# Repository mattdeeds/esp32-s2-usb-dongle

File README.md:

# esp32-s2-usb-dongle
 Simple USB A dongle with ESP32-S2-WROVER module for usb peripheral emulation

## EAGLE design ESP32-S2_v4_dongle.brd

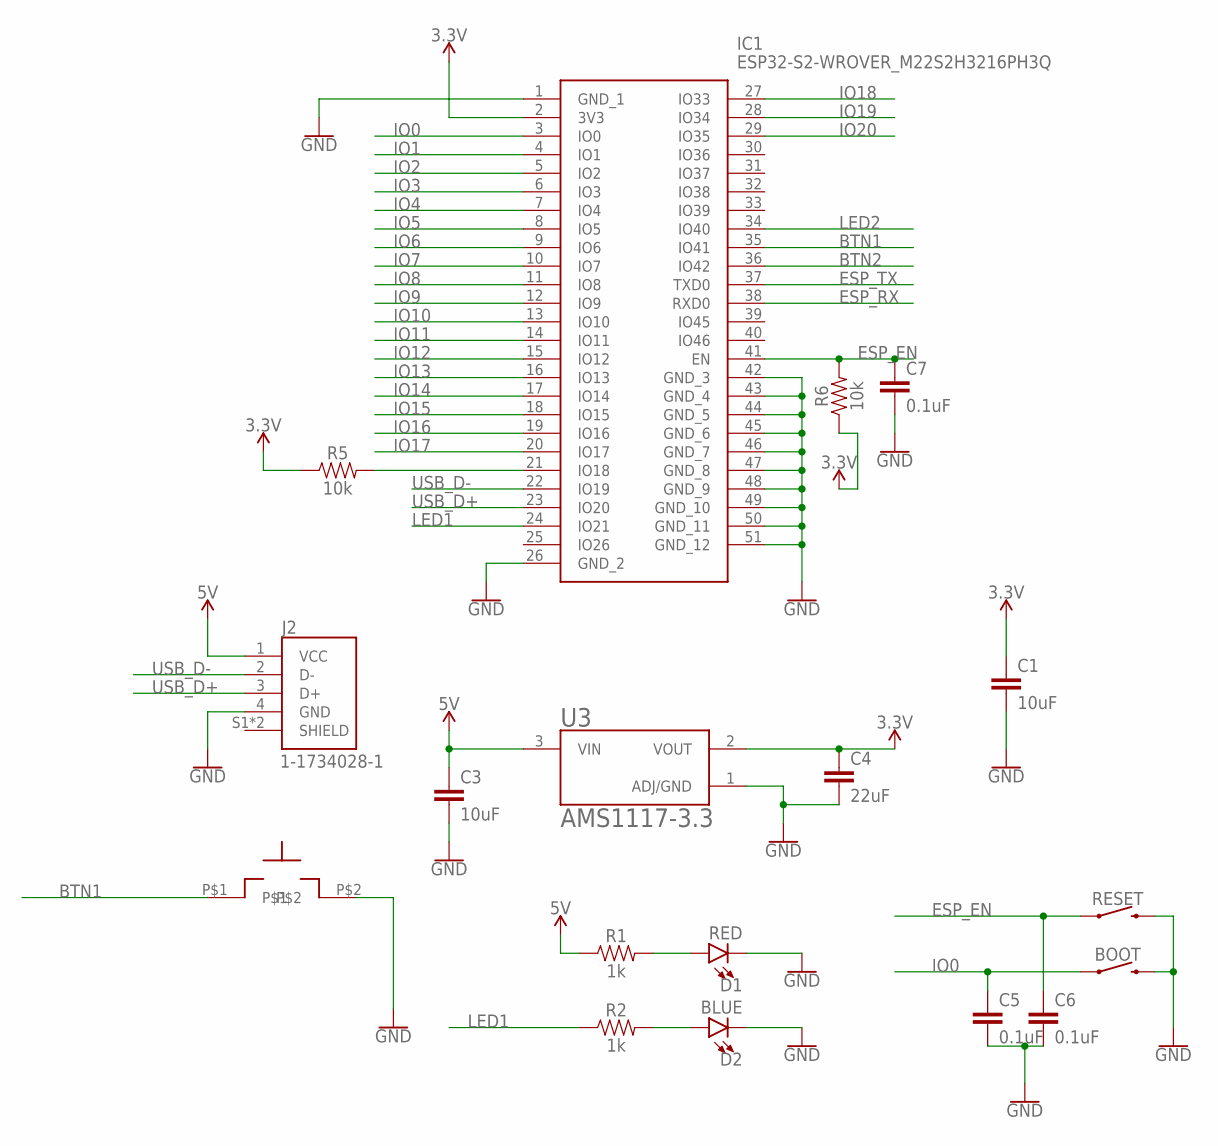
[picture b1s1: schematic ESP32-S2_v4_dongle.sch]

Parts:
BOOT: MOMENTARY-SWITCH-SPST-SMD-4.6X2.8MM; TACTILE_SWITCH_SMD_4.6X2.8MM
C1, C3: 10uF; 0603
C4: 22uF; 0603
C5, C6, C7: 0.1uF; 0603
D1: RED; LED-0603
D2: BLUE; LED-0603
IC1: ESP32-S2-WROVER_M22S2H3216PH3Q; ESP32S2WROVERM22S2H3216PH3Q0
J2: 1-1734028-1; TE_1-1734028-1
R1, R2: 1k; 0603
R5, R6: 10k; 0603
RESET: MOMENTARY-SWITCH-SPST-SMD-4.6X2.8MM; TACTILE_SWITCH_SMD_4.6X2.8MM
U3: AMS1117-3.3; SOT229P700X180-4N
U$1: TL9320AF400QG

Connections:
3.3V: C1.1, C4.1, IC1.2 (3V3), R5.1, R6.1, U3.2 (VOUT)
5V: C3.1, J2.1 (VCC), R1.1, U3.3 (VIN)
BTN1: IC1.35 (IO41), U$1.P$1
BTN2: IC1.36 (IO42)
ESP_EN: C6.1, C7.1, IC1.41 (EN), R6.2, RESET.1, RESET.2 (1)
ESP_RX: IC1.38 (RXD0)
ESP_TX: IC1.37 (TXD0)
GND: BOOT.3 (2), BOOT.4 (2), C1.2, C3.2, C4.2, C5.2, C6.2, C7.2, D1.C, D2.C, IC1.1 (GND_1), IC1.26 (GND_2), IC1.42 (GND_3), IC1.43 (GND_4), IC1.44 (GND_5), IC1.45 (GND_6), IC1.46 (GND_7), IC1.47 (GND_8), IC1.48 (GND_9), IC1.49 (GND_10), IC1.50 (GND_11), IC1.51 (GND_12), J2.4 (GND), RESET.3 (2), RESET.4 (2), U3.1 (ADJ/GND), U$1.P$2
IO0: BOOT.1, BOOT.2 (1), C5.1, IC1.3 (IO0)
IO1: IC1.4 (IO1)
IO2: IC1.5 (IO2)
IO3: IC1.6 (IO3)
IO4: IC1.7 (IO4)
IO5: IC1.8 (IO5)
IO6: IC1.9 (IO6)
IO7: IC1.10 (IO7)
IO8: IC1.11 (IO8)
IO9: IC1.12 (IO9)
IO10: IC1.13 (IO10)
IO11: IC1.14 (IO11)
IO12: IC1.15 (IO12)
IO13: IC1.16 (IO13)
IO14: IC1.17 (IO14)
IO15: IC1.18 (IO15)
IO16: IC1.19 (IO16)
IO17: IC1.20 (IO17)
IO18: IC1.27 (IO33)
IO19: IC1.28 (IO34)
IO20: IC1.29 (IO35)
LED1: IC1.24 (IO21), R2.1
LED2: IC1.34 (IO40)
unnamed: D1.A, R1.2
unnamed: D2.A, R2.2
unnamed: IC1.21 (IO18), R5.2
SHIELD: J2.S1 (SHIELD), J2.S2 (SHIELD)
USB_D+: IC1.23 (IO20), J2.3 (D+)
USB_D-: IC1.22 (IO19), J2.2 (D-)

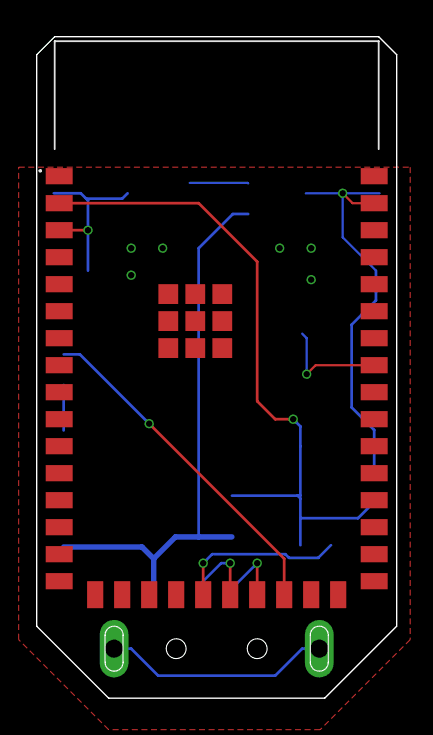
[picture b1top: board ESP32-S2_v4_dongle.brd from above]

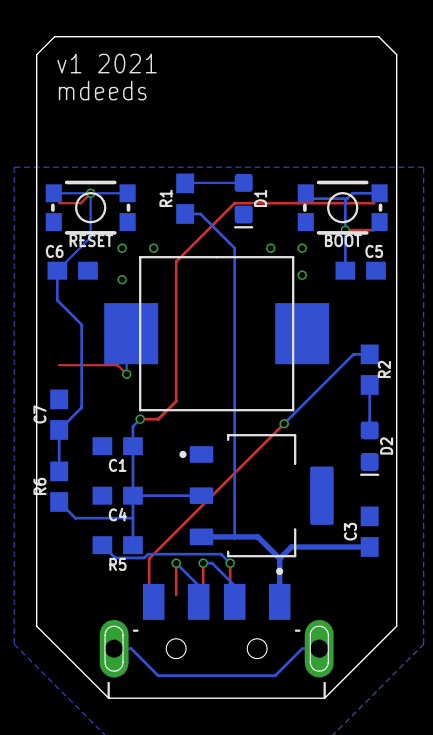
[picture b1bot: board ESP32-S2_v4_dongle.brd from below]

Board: 2 copper layers, 20.0 x 36.8 mm, 18 parts (17 on the bottom side), 13 nets.

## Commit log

2022-03-30 first
    added eagle sch, brd, and gerber files
2022-03-30 added BOM file

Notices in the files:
parts and their libraries:
SparkFun-LED: Licensing: Creative Commons ShareAlike 4.0 International - https://creativecommons.org/licenses/by-sa/4.0
